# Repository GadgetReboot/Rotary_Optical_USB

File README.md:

# Rotary_Optical_USB
Pi Pico USB Mouse/Keyboard for Arcade Trackball/Spinner and LS30 Mechanical Rotary Joysticks
<br><br><br><br>

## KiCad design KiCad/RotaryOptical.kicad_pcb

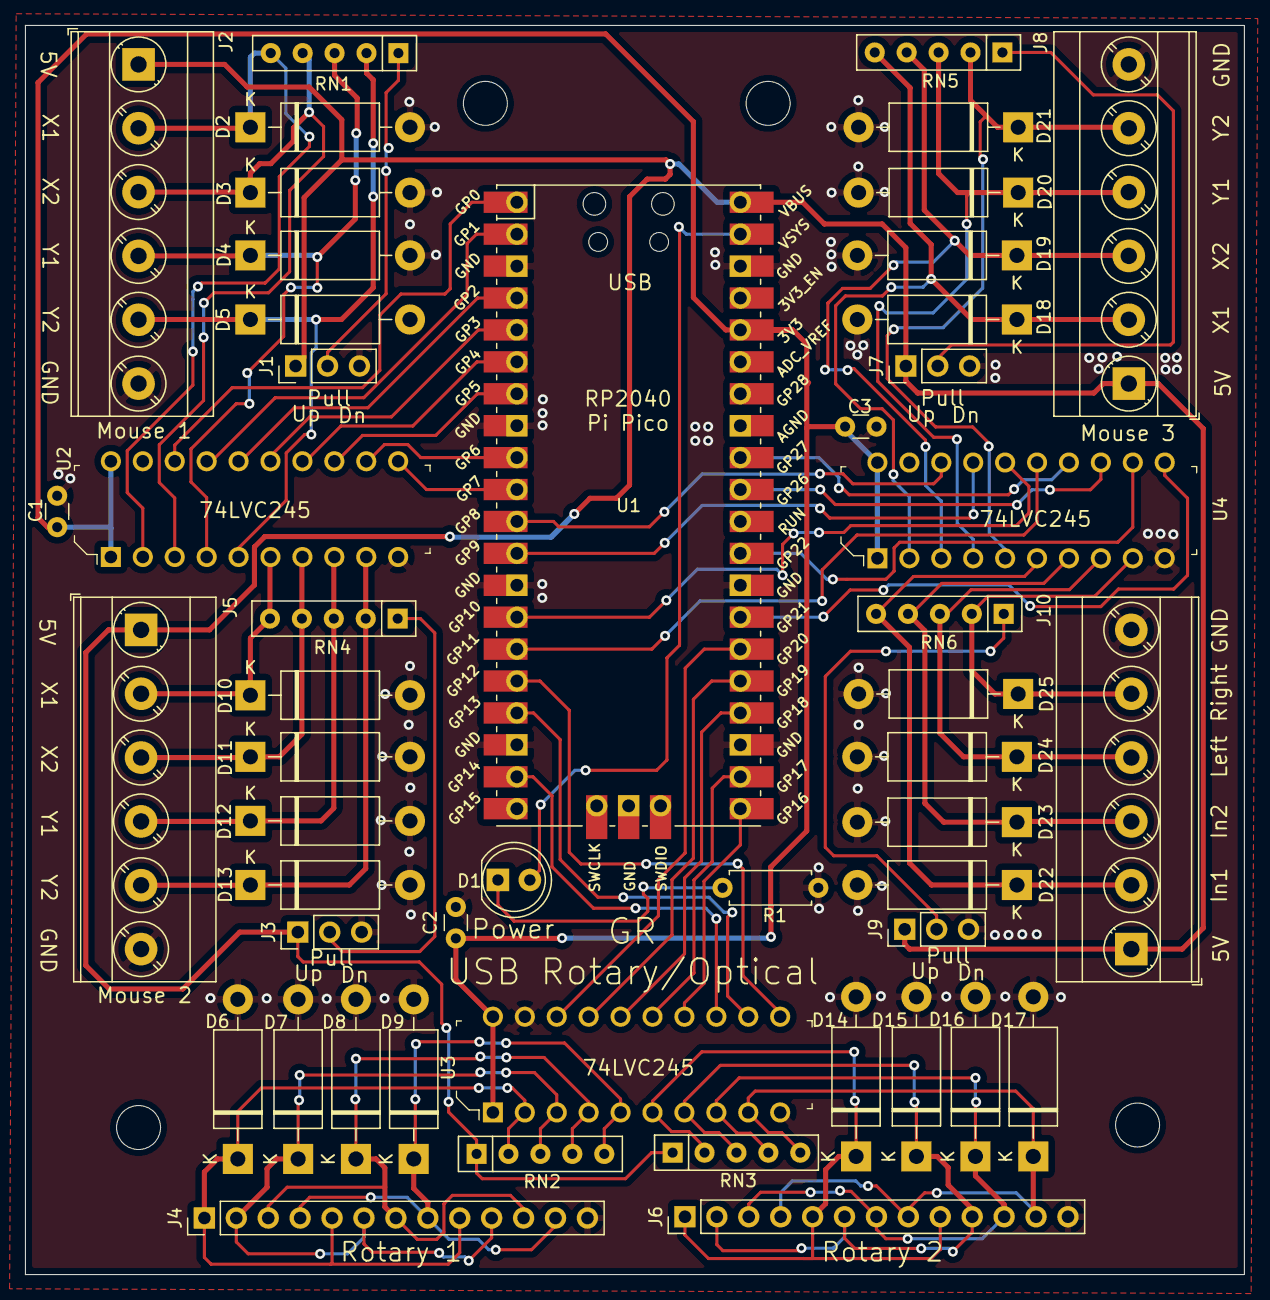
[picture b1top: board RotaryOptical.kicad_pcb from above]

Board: 2 copper layers, 97.0 x 99.4 mm, 53 parts (0 on the bottom side), 57 nets.

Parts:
C1, C2, C3: 100nF; C_Disc_D3.0mm_W1.6mm_P2.50mm
D1: LED_Small_ALT; LED_D5.0mm_Clear
D2, D3, D4, D5, D6, D7, D8, D9, D10, D11, D12, D13, D14, D15, D16, D17, D18, D19, D20, D21, D22, D23, D24, D25: SA5.0A; D_DO-15_P12.70mm_Horizontal
H1, H2, H3, H4: MountingHole; MountingHole_3.5mm
J1, J3, J7, J9: Conn_01x03; PinHeader_1x03_P2.54mm_Vertical
J2, J5, J8, J10: Screw_Terminal_01x06; TerminalBlock_Phoenix_MKDS-3-6-5.08_1x06_P5.08mm_Horizontal
J4, J6: Conn_01x13; PinHeader_1x13_P2.54mm_Vertical
R1: 470r; R_Axial_DIN0207_L6.3mm_D2.5mm_P7.62mm_Horizontal
RN1, RN2, RN3, RN4, RN5, RN6: 10K; R_Array_SIP5
U1: Pico; RPi_Pico_SMD_TH
U2, U3, U4: SN74LVC245AN; DIP-20_W7.62mm

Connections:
/3V3: C1.1, C2.1, C3.1, U1.36, U2.1, U2.20, U3.1, U3.20, U4.1, U4.20
/GP0: U1.1, U2.18
/GP1: U1.2, U2.17
/GP2: U1.4, U2.16
/GP3: U1.5, U2.15
/GP4: U1.6, U2.14
/GP5: U1.7, U2.13
/GP6: U1.9, U2.12
/GP7: U1.10, U2.11
/GP8: U1.11, U4.18
/GP9: U1.12, U4.17
/GP10: U1.14, U4.16
/GP11: U1.15, U4.15
/GP12: U1.16, U3.11
/GP13: U1.17, U3.12
/GP14: U1.19, U3.13
/GP16: U1.21, U3.14
/GP17: U1.22, U3.15
/GP18: U1.24, U3.16
/GP19: U1.25, U3.17
/GP20: U1.26, U3.18
/GP21: U1.27, U4.11
/GP22: U1.29, U4.12
/GP26_ADC0: U1.31, U4.13
/GP27_ADC1: U1.32, U4.14
/VBUS: J1.1, J2.1, J3.1, J5.1, J7.1, J8.1, J9.1, J10.1, RN2.1, RN3.1, U1.40
/VSYS: D1.2, U1.39
GND: C1.2, C2.2, C3.2, D2.2, D3.2, D4.2, D5.2, D6.2, D7.2, D8.2, D9.2, D10.2, D11.2, D12.2, D13.2, D14.2, D15.2, D16.2, D17.2, D18.2, D19.2, D20.2, D21.2, D22.2, D23.2, D24.2, D25.2, J1.3, J2.6, J3.3, J4.13, J5.6, J6.13, J7.3, J8.6, J9.3, J10.6, R1.2, U1.3, U1.8, U1.13, U1.18, U1.23, U1.28, U1.38, U2.10, U2.19, U3.10, U3.19, U4.10, U4.19
unnamed: D1.1, R1.1
unnamed: D2.1, J2.2, RN1.5, U2.2
unnamed: D3.1, J2.3, RN1.4, U2.3
unnamed: D4.1, J2.4, RN1.3, U2.4
unnamed: D5.1, J2.5, RN1.2, U2.5
unnamed: D6.1, J4.1, J4.5, J4.9, RN2.2, U3.2
unnamed: D7.1, J4.2, J4.6, J4.10, RN2.3, U3.3
unnamed: D8.1, J4.3, J4.7, J4.11, RN2.4, U3.4
unnamed: D9.1, J4.4, J4.8, J4.12, RN2.5, U3.5
unnamed: D10.1, J5.2, RN4.5, U2.6
unnamed: D11.1, J5.3, RN4.4, U2.7
unnamed: D12.1, J5.4, RN4.3, U2.8
unnamed: D13.1, J5.5, RN4.2, U2.9
unnamed: D14.1, J6.1, J6.5, J6.9, RN3.2, U3.6
unnamed: D15.1, J6.2, J6.6, J6.10, RN3.3, U3.7
unnamed: D16.1, J6.3, J6.7, J6.11, RN3.4, U3.8
unnamed: D17.1, J6.4, J6.8, J6.12, RN3.5, U3.9
unnamed: D18.1, J8.2, RN5.5, U4.2
unnamed: D19.1, J8.3, RN5.4, U4.3
unnamed: D20.1, J8.4, RN5.3, U4.4
unnamed: D21.1, J8.5, RN5.2, U4.5
unnamed: D22.1, J10.2, RN6.5, U4.6
unnamed: D23.1, J10.3, RN6.4, U4.7
unnamed: D24.1, J10.4, RN6.3, U4.8
unnamed: D25.1, J10.5, RN6.2, U4.9
unnamed: J1.2, RN1.1
unnamed: J3.2, RN4.1
unnamed: J7.2, RN5.1
unnamed: J9.2, RN6.1

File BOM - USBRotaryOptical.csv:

USB Rotary Joystick/Trackball BOM,,,,,,,,
,,,,,,,,
Item #,Reference Designator,Qty,Manufacturer,Mfg Part #,Description / Value,Package/Footprint ,Type,Instructions / Notes
1,C1 C2 C3,3,KEMET,C320C104K5R5TA7317,0.1 µF ±10% 50V Ceramic Capacitor X7R Radial,2.5mm Pitch,THRU-HOLE,
2,D1,1,Kingbright,WP7113ID,LED RED DIFFUSED T-1 3/4 T/H,T-1 3/4,THRU-HOLE,
3,D2 D3 D4 D5 D6 D7 D8 D9 D10 D11 D12 D13 D14 D15 D16 D17 D18 D19 D20 D21 D22 D23 D24 D25,24,"	
Littelfuse Inc.",SA5.0A,TVS DIODE 5VWM 9.2VC DO204AC,DO-15,THRU-HOLE,
4,J1 J3 J7 J9,4,Sullins Connector Solutions,PREC003SAAN-RC,"Connector Header Through Hole 3 position 0.100""",3POS,THRU-HOLE,
5,J4 J6,2,XKB Connectivity,X6511WR-13H-C30D60R1,Connector Header Through Hole 1x13P P=2.54mm,13POS,THRU-HOLE,
6,J2 J5 J8 J10,4,Phoenix Contact,1729160,TERM BLK 6P SIDE ENT 5.08MM PCB,6POS,THRU-HOLE,
7,R1,1,YAGEO,CFR-25JR-52-330R,RES 330 OHM 5% 1/4W AXIAL,Axial,THRU-HOLE,
8,RN1 RN2 RN3 RN4 RN5 RN6,6,FH (Guangdong Fenghua Advanced Tech),A05-103JP,±5% 4x10kΩ 125mW SIP-5-2.54mm Resistor Network,SIP-5-2.54mm,THRU-HOLE,
9,U1,2,Sullins Connector Solutions,"	
PPTC201LFBN-RC",CONN HDR 20POS 0.1 TIN PCB,20POS,THRU-HOLE,"U1 should be populated with two 20 pin headers to let the user plug in a ""Raspberry Pi Pico"" module"
10,U2 U3 U4,3,Texas Instruments,SN74LVC245AN,"Transceiver, Non-Inverting 8 Bit 3-State Output 20-PDIP",DIP-20,THRU-HOLE,
,,,,,,,,
Note:  The BOM does not list the Raspberry Pi Pico module required to plug into the female header pins of U1.  The user is assumed to supply their own module.,,,,,,,,
